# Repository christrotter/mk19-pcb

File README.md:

# mk19-pcb
The antithesis of 'keep it simple, stupid' - all the features, all the time.

Do you need...
- To use the [Cyboard flex-pcb system](https://www.cyboard.digital/product-page/dactyl-flex-pcbs)?  [and extend it?](https://github.com/christrotter/macropad-pcb)?
- Two [Ultrafalcons](https://github.com/christrotter/ultrafalcon)...per side?
- SPI devices
  - PMW3360/3389 (_right side only_)
  - Dual GC9A01 TFTs per side
  - Quad-shift register-powered 32 pins for rows/cols? ([available as a dedicated breakout here](https://github.com/christrotter/shift-register-spi-breakout-pcb))
- [5-way switch](https://github.com/christrotter/5way-pcb) or [RKJXT](https://github.com/christrotter/rkjxt-mini-breakout) for arrow keys?
- Perhaps enough RGB to illumine your entire home? (_and almost certainly require 5v supplementary power - a feature, not a bug!_)  
- Audio and ADC breakouts?  Reset switch? Power and debug breakouts?
- And use an existing RP Pico to do it?

...probably not, which is why I had to design my own pcb.  So here it is...

# the community that built it
- burkfers (research assistant extraordinaire)
- bomtarnes, chefcooke, walrus, wimads, yingeling, genki, others for design/3d printing help
- Quentin @ BKB & Erik @ Cyboard
- casuanoob (Falcon and diy pcb inspiration)
- tzarc, freznel, KarlK90, Dr. Faustroll, GeorgeN, (and others!) work on shift registers, pcbs, etc
- BKB discord crew; QMK discord; fingerpunch discord (Sadek and Melon, thanks!)
- cardiactuna for the font suggestion

# rev2 improvements
- added rkjxt to dpad connector
- added resistor networks for col shift register pulldown
- relocated cyboard connectors
- fixed a bunch of incorrect pinout orderings
- changed from solder pads to pin jumpers
- re-thought led bypass
- moved TFTs to FFC cables, made 3 of them
- added external 5v power source option
- re-thought the test pins

# design goals
- Provide a re-usable platform for the arcboards
- Make it possible to use the Cyboard flex-pcb system to save on the madness of per-key pcb soldering
- Minimize GPIO usage by moving cols/rows over to shift registers
- Reduce the amount of fiddly soldering and wire stripping a normal hand-wire build requires of you
- USB-C interconnects
- General improvements on the mk17 as a whole

## feature details
- Raspberry PI Pico (RP2040) footprint - just add pin headers and solder away - or, solder directly to pads
- keys provided through the [Cyboard flex-pcb system](https://www.cyboard.digital/product-page/dactyl-flex-pcbs) or, JST-XH 2.54 headers
- macropad using Cyboard flex-pcb keys, custom breakout pcb: https://github.com/christrotter/macropad-pcb (0.5mm pitch 16-pin FFC cable)
  - in future I'd just make this a custom FPC cable
- dpad using custom breakout pcbs [5-way switch](https://github.com/christrotter/5way-pcb) or [RKJXT](https://github.com/christrotter/rkjxt-mini-breakout)
 - diodes are configured for ROW2COL (_to match Cyboard_)
- USB-C split connector w. tzarc-grade voltage protection
 - included a solder pad jumper to bypass if needed
- split-handedness via pin (jumper)
- SPI breakouts
  - PMW33xx
  - 3x TFT LCD (e.g. GC9A01)
  - shift registers (595 for rows, 589 for cols)
- pin breakouts
 - power, debug, ADC, audio, reset
 - remaining GPIO pins
 - test points
- led breakouts w. bypasses
 - keys
 - 2x falcon pcbs
 - indicator strip
 - screen-mounted external indicators via USB-C
  - this passes 5v/GND, level-shifted 5v LED DI/DO signal via USB-C cable
 - pin for whatever else you want to add to the chain

## pcb features

- two-layer pcb w. dual ground planes tied w. vias
- components configured as per datasheets
- bypass capacitors!
- care taken to avoid power running alongside signal for too long

# schematic overview
## mcu

## keys via shift registers

## peripherals

## usb connections

## breakouts

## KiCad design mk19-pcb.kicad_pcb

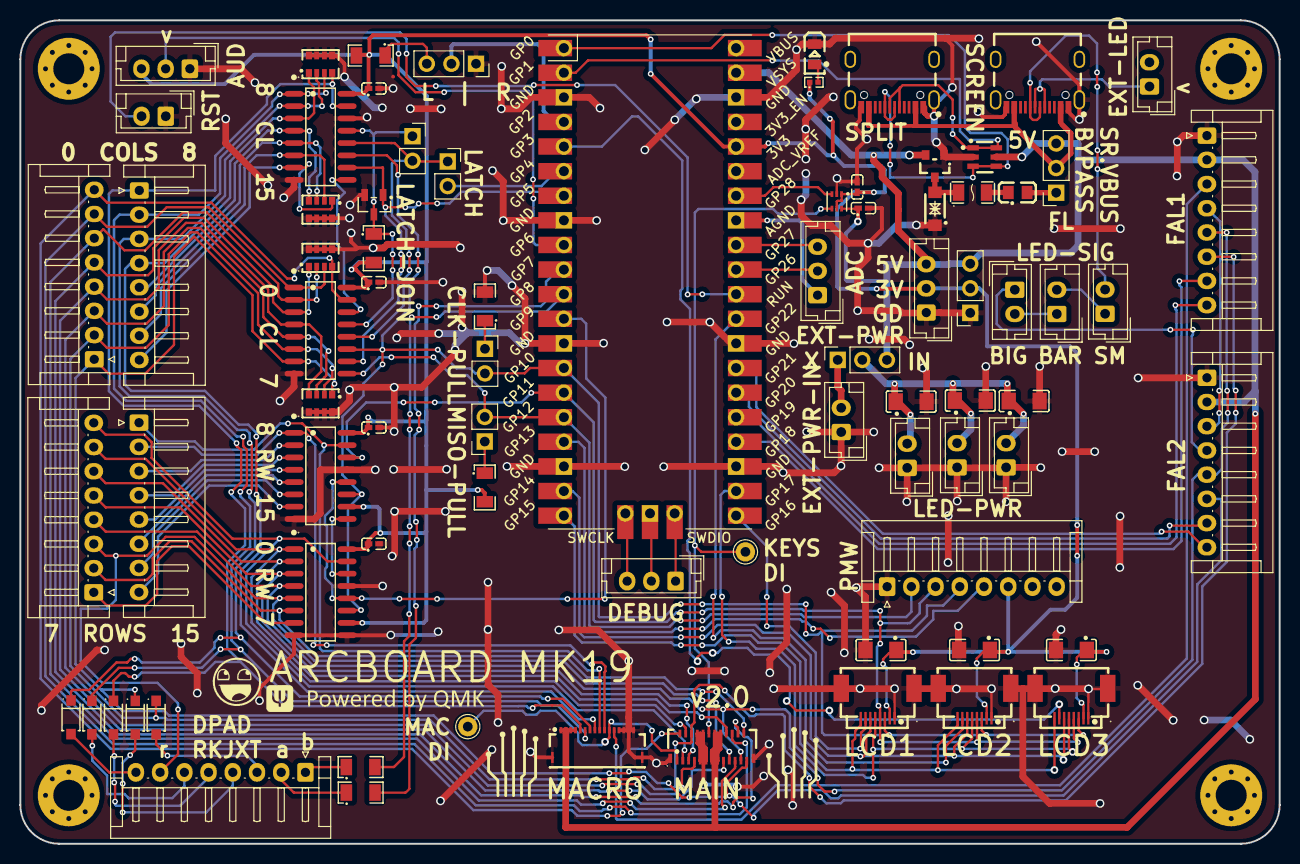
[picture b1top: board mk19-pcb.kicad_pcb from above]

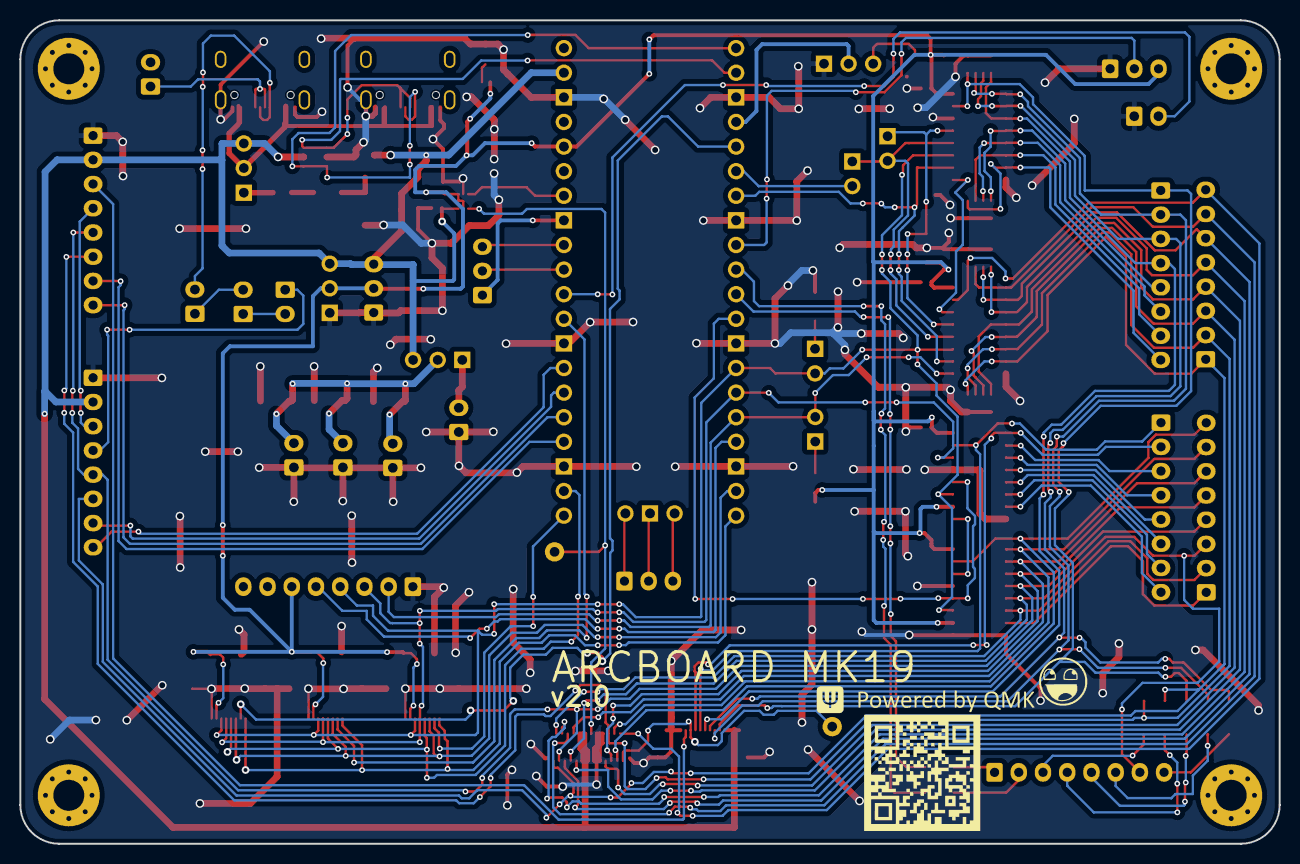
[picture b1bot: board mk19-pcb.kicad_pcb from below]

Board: 2 copper layers, 130.0 x 85.0 mm, 90 parts (3 on the bottom side), 96 nets.

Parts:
5WAY1: Conn_01x08_Socket; JST_EH_S8B-EH_1x08_P2.50mm_Horizontal
ADC1: Conn_01x03_Socket; JST_EH_B3B-EH-A_1x03_P2.50mm_Vertical
AUDIO1: Conn_01x03_Socket; JST_EH_B3B-EH-A_1x03_P2.50mm_Vertical
C1, C2, C3, C4, C5, C6: 100nF; C0402
C7, C8, C9, C10, C11, C12: CL31B105KBHNNNE; C1206
CLK_PULL1: Conn_01x02_Socket; PinSocket_1x02_P2.54mm_Vertical
COL1, COL2: Conn_01x08_Socket; JST_EH_S8B-EH_1x08_P2.50mm_Horizontal
COL_CS_MOS1: 2N7002; SOT-23-3_L2.9-W1.3-P1.90-LS2.4-BR
COL_JOIN1, COL_JOIN2: Conn_01x02_Socket; PinSocket_1x02_P2.54mm_Vertical
CYBOARD-MACRO1: HC-FPC-05-10-16RLTAG; FPC-SMD_16P-P0.50_HCTL_HC-FPC-05-10-16RLTAG
CYBOARD-MAIN1: ECT818001569; FPC-SMD_ECT818001569
D1: SMF5_0CA_C364279; SOD-123FL_L2.8-W1.8-LS3.7-BI
DBG1: Conn_01x03_Socket; JST_EH_B3B-EH-A_1x03_P2.50mm_Vertical
F1: MF-NSMF075-2; F1206
FAL1, FAL2: Conn_01x08_Socket; JST_EH_S8B-EH_1x08_P2.50mm_Horizontal
H1, H2, H3, H4: MountingHole; MountingHole_3.2mm_M3_Pad_Via
J1, J2, J4, J7, J9, J10, J11: Conn_01x02_Socket; JST_EH_B2B-EH-A_1x02_P2.50mm_Vertical
L1: MPZ2012S101AT000; L0805
LED1: 0805G_(Green); LED0805-R-RD
LED-LVL1: SN74LVC1T45DRL; SOT-563_L1.6-W1.2-P0.50-LS1.6-BR
LOGO1, LOGO3: **REF; awesome-logo
LOGO2, LOGO4: **REF; qmk-lite
LOGO5: **REF; mk19-qr-logo-12mm
LOGO6, LOGO7: **REF; cyboard-logo-10mm
MISO_PULL1: Conn_01x02_Socket; PinSocket_1x02_P2.54mm_Vertical
MOSFET1: AO3401A_C347476; SOT-23_L2.9-W1.3-P1.90-LS2.4-BR
PICO1: Pico; RPi_Pico_SMD_TH
PWM1: Conn_01x08_Socket; JST_EH_S8B-EH_1x08_P2.50mm_Horizontal
PWR-EXT-IN1: Conn_01x02_Socket; JST_EH_B2B-EH-A_1x02_P2.50mm_Vertical
PWR-OUT1: Conn_01x03_Socket; JST_EH_B3B-EH-A_1x03_P2.50mm_Vertical
PWR-OUT2, PWR-OUT6: Conn_01x03_Socket; PinSocket_1x03_P2.54mm_Vertical
R1, R10, R11: 1206W4F1002T5E; R1206
R2, R3, R4, R5: 4D03WGJ0103T5E; RES-ARRAY-SMD_0603-8P-L3.2-W1.6-BL
R6, R7, R8: 4.7k; R1206
R9: 0402WGF2001TCE; R0402
REG-COL1, REG-COL2: MC74HC589ADR2G; SOIC-16_L9.9-W3.9-P1.27-LS6.0-BL
REG-ROW1, REG-ROW2: 74HC595D; SOIC-16_L9.9-W3.9-P1.27-LS6.0-BL
RESET1: Conn_01x02_Socket; JST_EH_B2B-EH-A_1x02_P2.50mm_Vertical
ROW1, ROW2: Conn_01x08_Socket; JST_EH_S8B-EH_1x08_P2.50mm_Horizontal
SCREEN1: TYPE-C-31-M-12; USB-C_SMD-TYPE-C-31-M-12
SPLIT-USB1: TYPE-C-31-M-12; USB-C_SMD-TYPE-C-31-M-12
SPLIT_HAND1: Conn_01x03_Socket; PinSocket_1x03_P2.54mm_Vertical
T1, T10: Conn_01x01_Socket; Pin_D1.0mm_L10.0mm
U1: AZC199-04S-MS; TSOT-23-6_L2.9-W1.6-P0.95-LS2.8-BL
U2, U3, U4, U5, U6: 1N4148W_C81598; SOD-123F_L2.7-W1.6-LS3.8-RD
U9, U10, U11: 8_01A0_008200; FPC-SMD_8P-P0.50_8.01A0.008200
VCC_BYPASS1: Conn_01x03_Socket; PinSocket_1x03_P2.54mm_Vertical

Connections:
+3V3: AUDIO1.3, C1.1, C2.1, C3.1, C4.1, C5.1, C10.1, C11.1, C12.1, LED-LVL1.1 (VCCA), LED-LVL1.5 (DIR), PICO1.36 (3V3), PWM1.6, PWR-OUT1.2, PWR-OUT2.2, R1.2, R9.1, R10.2, R11.2, REG-COL1.16 (VCC), REG-COL2.16 (VCC), REG-ROW1.10 (MasterReset), REG-ROW1.16 (VCC), REG-ROW2.10 (MasterReset), REG-ROW2.16 (VCC), U9.2, U10.2, U11.2
AGND: ADC1.1, PICO1.33 (AGND)
COL_CS: COL_CS_MOS1.1 (G), PICO1.7 (GPIO5), REG-COL1.10 (OE), REG-COL2.10 (OE)
COL_CS_MOS: COL_CS_MOS1.3 (D), COL_JOIN1.1, R1.1, REG-COL1.13 (SLOAD), REG-COL2.13 (SLOAD)
COL_LATCH: COL_JOIN2.2, PICO1.6 (GPIO4)
GND: AUDIO1.1, C1.2, C2.2, C3.2, C4.2, C5.2, C6.2, C7.2, C8.2, C9.2, C10.2, C11.2, C12.2, COL_CS_MOS1.2 (S), CYBOARD-MACRO1.13, CYBOARD-MACRO1.14, CYBOARD-MACRO1.15, CYBOARD-MACRO1.16, CYBOARD-MACRO1.17, CYBOARD-MACRO1.18, CYBOARD-MAIN1.8, CYBOARD-MAIN1.9, CYBOARD-MAIN1.10, CYBOARD-MAIN1.11, CYBOARD-MAIN1.26, CYBOARD-MAIN1.27, D1.1 (K), FAL1.1, FAL2.1, J1.1, J2.1, J7.1, LED1.2 (K), LED-LVL1.2 (GND), MOSFET1.1 (G), PICO1.3 (GND), PICO1.8 (GND), PICO1.13 (GND), PICO1.18 (GND), PICO1.23 (GND), PICO1.28 (GND), PICO1.38 (GND), PWM1.1, PWR-EXT-IN1.1, PWR-OUT1.1, PWR-OUT2.1, R2.5, R2.6, R2.7, R2.8, R3.5, R3.6, R3.7, R3.8, R4.5, R4.6, R4.7, R4.8, R5.5, R5.6, R5.7, R5.8, R8.2, REG-COL1.8 (GND), REG-COL2.8 (GND), REG-COL2.14 (SA), REG-ROW1.8 (GND), REG-ROW1.9 (Q7S), REG-ROW1.13 (OutputEnable), REG-ROW2.8 (GND), REG-ROW2.13 (OutputEnable), RESET1.1, SCREEN1.0 (SH), SCREEN1.A1 (GND), SCREEN1.A12 (GND), SCREEN1.B1 (GND), SCREEN1.B12 (GND), SPLIT-USB1.0 (SH), SPLIT-USB1.A1 (GND), SPLIT-USB1.A12 (GND), SPLIT-USB1.B1 (GND), SPLIT-USB1.B12 (GND), SPLIT_HAND1.1, U1.2, U9.1, U9.9, U9.10, U10.1, U10.9, U10.10, U11.1, U11.9, U11.10
GPIO6: AUDIO1.2, PICO1.9 (GPIO6)
GPIO26: ADC1.2, PICO1.31 (GPIO26_ADC0)
GPIO27: ADC1.3, PICO1.32 (GPIO27_ADC1)
LCD1_CS: PICO1.21 (GPIO16), U9.7
LCD2_CS: PICO1.29 (GPIO22), U10.7
LCD3_CS: PICO1.5 (GPIO3), U11.7
LCD_BL: PICO1.20 (GPIO15), U9.8, U10.8, U11.8
LCD_DC: PICO1.19 (GPIO14), U9.6, U10.6, U11.6
LCD_RST: PICO1.22 (GPIO17), U9.5, U10.5, U11.5
LED_5V: C7.1, C8.1, C9.1, J1.2, J2.2, J7.2, PWR-OUT6.2
LED_DI_3v3: LED-LVL1.3 (A), PICO1.34 (GPIO28_ADC2)
LED_FAL1_DI: CYBOARD-MACRO1.12, FAL1.3
LED_FAL2_DI: FAL1.4, FAL2.3
LED_KEYBAR_DI: J4.1, J10.2
LED_KEYS_DI: CYBOARD-MAIN1.12, LED-LVL1.4 (B), T10.1
LED_MACRO_DI: CYBOARD-MACRO1.11, CYBOARD-MAIN1.1, T1.1
LED_SCREEN_DI: J9.2, SCREEN1.A6 (DP1), SCREEN1.B6 (DP2)
LED_SCREEN_DO: J11.1, SCREEN1.A7 (DN1), SCREEN1.B7 (DN2)
LED_SLATS_BIG_DI: FAL2.4, J10.1
LED_SLATS_SM_DI: J4.2, J9.1
unnamed: 5WAY1.1, R7.1
unnamed: 5WAY1.2, R6.1
unnamed: 5WAY1.3, U4.2 (A)
unnamed: 5WAY1.4, U6.2 (A)
unnamed: 5WAY1.5, U3.2 (A)
unnamed: 5WAY1.6, U5.2 (A)
unnamed: 5WAY1.8, U2.2 (A)
unnamed: CLK_PULL1.1, R8.1
unnamed: COL_JOIN1.2, COL_JOIN2.1, REG-COL1.12 (LATCH_CLOCK), REG-COL2.12 (LATCH_CLOCK)
unnamed: D1.2 (A), F1.1, MOSFET1.3 (D)
unnamed: F1.2, L1.1
unnamed: LED1.1 (A), R9.2
unnamed: MISO_PULL1.1, R10.1
unnamed: PICO1.4 (GPIO2), SPLIT_HAND1.2
unnamed: PWR-EXT-IN1.2, PWR-OUT6.1
unnamed: REG-COL1.14 (SA), REG-COL2.9 (QH)
unnamed: REG-ROW1.14 (DS), REG-ROW2.9 (Q7S)
unnamed: R11.1, SPLIT_HAND1.3
unnamed: L1.2, VCC_BYPASS1.1
PMW_CS: PICO1.17 (GPIO13), PWM1.5
ROW_CS: PICO1.12 (GPIO9), REG-ROW1.12 (StorageClock), REG-ROW2.12 (StorageClock)
SPI1_CLK: CLK_PULL1.2, PICO1.14 (GPIO10), PWM1.4, REG-COL1.11 (SHIFT_CLOCK), REG-COL2.11 (SHIFT_CLOCK), REG-ROW1.11 (ShiftClock), REG-ROW2.11 (ShiftClock), U9.3, U10.3, U11.3
SPI1_MISO: MISO_PULL1.2, PICO1.16 (GPIO12), PWM1.2, REG-COL1.9 (QH)
SPI1_MOSI: PICO1.15 (GPIO11), PWM1.3, REG-ROW2.14 (DS), U9.4, U10.4, U11.4
SWCLK: DBG1.3, PICO1.41 (SWCLK)
SWDIO: DBG1.1, PICO1.43 (SWDIO)
SWGND: DBG1.2, PICO1.42 (GND)
Serial_VBUS: SCREEN1.A4 (VBUS), SCREEN1.A9 (VBUS), SCREEN1.B4 (VBUS), SCREEN1.B9 (VBUS), SPLIT-USB1.A4 (VBUS), SPLIT-USB1.A9 (VBUS), SPLIT-USB1.B4 (VBUS), SPLIT-USB1.B9 (VBUS), VCC_BYPASS1.2
Split_Comms_RX: PICO1.2 (GPIO1), SPLIT-USB1.A7 (DN1), SPLIT-USB1.B7 (DN2), U1.1, U1.6
Split_Comms_TX: PICO1.1 (GPIO0), SPLIT-USB1.A6 (DP1), SPLIT-USB1.B6 (DP2), U1.3, U1.4
VCC: C6.1, CYBOARD-MACRO1.1, CYBOARD-MACRO1.2, CYBOARD-MACRO1.3, CYBOARD-MACRO1.4, CYBOARD-MAIN1.13, CYBOARD-MAIN1.14, CYBOARD-MAIN1.15, CYBOARD-MAIN1.16, FAL1.2, FAL2.2, LED-LVL1.6 (VCCB), MOSFET1.2 (S), PICO1.39 (VSYS), PWR-OUT1.3, PWR-OUT2.3, PWR-OUT6.3, U1.5, VCC_BYPASS1.3
col0: COL1.8, CYBOARD-MAIN1.2, R3.4, REG-COL1.15 (A)
col1: COL1.7, CYBOARD-MAIN1.20, R3.3, REG-COL1.1 (B)
col2: COL1.6, CYBOARD-MAIN1.21, R3.2, REG-COL1.2 (C)
col3: COL1.5, CYBOARD-MAIN1.22, R3.1, REG-COL1.3 (D)
col4: COL1.4, CYBOARD-MAIN1.17, R2.4, REG-COL1.4 (E)
col5: COL1.3, CYBOARD-MAIN1.7, R2.3, REG-COL1.5 (F)
col6: COL1.2, CYBOARD-MAIN1.6, FAL1.6, R2.2, REG-COL1.6 (G), U4.1 (K)
col7: COL1.1, CYBOARD-MAIN1.25, FAL2.6, R2.1, REG-COL1.7 (H), U6.1 (K)
col8: COL2.1, CYBOARD-MACRO1.5, R5.4, REG-COL2.15 (A), U3.1 (K)
col9: COL2.2, CYBOARD-MACRO1.6, R5.3, REG-COL2.1 (B), U5.1 (K)
col10: COL2.3, CYBOARD-MACRO1.7, R5.2, REG-COL2.2 (C), U2.1 (K)
col11: COL2.4, CYBOARD-MACRO1.8, R5.1, REG-COL2.3 (D)
col12: COL2.5, R4.4, REG-COL2.4 (E)
col13: COL2.6, R4.3, REG-COL2.5 (F)
col14: COL2.7, R4.2, REG-COL2.6 (G)
col15: COL2.8, R4.1, REG-COL2.7 (H)
fal1-r1: FAL1.7, PICO1.24 (GPIO18)
fal1-r2: FAL1.8, PICO1.25 (GPIO19)
fal2-r1: FAL2.7, PICO1.26 (GPIO20)
fal2-r2: FAL2.8, PICO1.27 (GPIO21)
reset: PICO1.30 (RUN), RESET1.2
rkjxt-a: PICO1.10 (GPIO7), R6.2
rkjxt-b: PICO1.11 (GPIO8), R7.2
row0: CYBOARD-MAIN1.3, REG-ROW1.15 (Q0), ROW1.8
row1: CYBOARD-MAIN1.4, REG-ROW1.1 (Q1), ROW1.7
row2: CYBOARD-MAIN1.18, REG-ROW1.2 (Q2), ROW1.6
row3: CYBOARD-MAIN1.5, REG-ROW1.3 (Q3), ROW1.5
row4: CYBOARD-MAIN1.23, FAL1.5, FAL2.5, REG-ROW1.4 (Q4), ROW1.4
row5: 5WAY1.7, CYBOARD-MAIN1.19, REG-ROW1.5 (Q5), ROW1.3
row6: CYBOARD-MAIN1.24, REG-ROW1.6 (Q6), ROW1.2
row7: REG-ROW1.7 (Q7), ROW1.1
row8: CYBOARD-MACRO1.9, REG-ROW2.15 (Q0), ROW2.1
row9: CYBOARD-MACRO1.10, REG-ROW2.1 (Q1), ROW2.2
row10: REG-ROW2.2 (Q2), ROW2.3
row11: REG-ROW2.3 (Q3), ROW2.4
row12: REG-ROW2.4 (Q4), ROW2.5
row13: REG-ROW2.5 (Q5), ROW2.6
row14: REG-ROW2.6 (Q6), ROW2.7
row15: REG-ROW2.7 (Q7), ROW2.8

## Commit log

2024-02-14 getting the schematic updated, adding missing features
2024-02-16 all new features added, fixes implemented, ready to start arranging and routing
2024-02-17 feb16 work, almost ready to start running traces
2024-02-17 first draft done - needs work on led signal flow, silkscreen, falcon row-col thing.
2024-02-18 ready for review
2024-02-18 missed cyboard branding, added a test pin for macro led DI
2024-02-18 more minor fixes
2024-02-18 adding jumper for clk pulldown
2024-02-19 production files
2024-02-21 just minor 3d file changes
2024-02-22 working on improving the readme
2024-02-28 updating readme
